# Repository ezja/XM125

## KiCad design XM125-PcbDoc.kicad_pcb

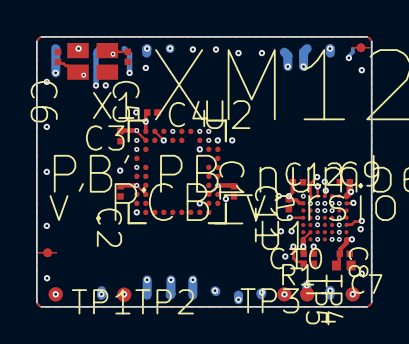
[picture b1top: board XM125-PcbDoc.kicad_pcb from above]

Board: 4 copper layers, 18.6 x 15.0 mm, 24 parts (1 on the bottom side), 28 nets.

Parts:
C1, C2, C3, C4, C12: Generic 1uF SMD capacitor, metric 0603 (0201); CAPC0603X04L_no_silkscreen
C5, C6: Generic 8pF SMD capacitor, metric 0603 (0201); CAPC0603X04L_no_silkscreen
C7: Generic 4.7uF SMD capacitor, metric 1005 (0402); CAPC1005X05L
C8, C9, C10, C11: Generic 100 nF SMD capacitor, metric 0603 (0201); CAPC0603X04L_no_silkscreen
F1, F2: Fiducial marker; Fiducial 0.5 mm footprint-1
J1: 28-pin Land Grid Array (LGA), pitch 1.27 mm; LCCS127P1500X1800X0-28N
R1: 100 kOhm generic SMD resistor, +/-1%, metric 0603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; RESC0603X03L_no_silkscreen
TP1, TP2, TP3, TP4, TP5: Circular test point; Testpoint_circular_0.8_no_silkscreen
U1: RISC Microcontroller, 32-Bit, FLASH, 80MHz, CMOS,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; BGA49C40P7X7_314X313X58
U2: Acconeer A121 pulsed coherent 60 GHz radar sensor; BGA50C50P10X10_520X550X90
X1: Crystal 24 MHz 2.5 x 2.0 mm 4-SMD; ECS-240-8-36-RWN-TR3-Footprint-No-Silk

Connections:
1V8_sensor: C1.1, C2.1, C3.1, J1.3, U2.C2, U2.C9, U2.D1, U2.D10, U2.J9
DEBUG_UART_RX: J1.21, U1.C2
DEBUG_UART_TX: J1.23, U1.D2
ENABLE: U1.F1, U2.F10
GND: C1.2, C2.2, C3.2, C4.2, C5.2, C6.2, C7.2, C8.2, C9.2, C10.2, C11.2, C12.2, J1.2, J1.4, J1.7, J1.10, J1.13, J1.16, J1.19, J1.22, J1.27, R1.1, TP2.1, U1.A6, U1.B1, U1.E7, U1.G2, U2.A2, U2.A3, U2.A4, U2.A5, U2.A6, U2.A7, U2.A8, U2.A9, U2.B1, U2.B2, U2.B9, U2.B10, U2.C1, U2.C10, U2.D2, U2.D9, U2.E1, U2.E2, U2.E9, U2.E10, U2.F1, U2.F2, U2.F9, U2.G1, U2.G10, U2.H1, U2.H2, U2.H9, U2.J3, U2.J5, U2.J6, U2.J8, U2.K4, U2.K5, U2.K7, X1.2, X1.4
I2C_ADDR: J1.20, U1.D7
I2C_SCL: J1.17, U1.E3
I2C_SDA: J1.18, U1.F2
INTERRUPT: U1.A3, U2.K8
MCU_INT: J1.28, U1.C5
MISC_GPIO0: J1.24, U1.G4
MISC_GPIO1: J1.25, U1.G6
MISC_GPIO2_BOOT0: J1.26, R1.2, U1.A5
NRESET: J1.14, TP5.1, U1.D5
SPI_CLK: U1.F5, U2.K2
SPI_MISO: U1.F4, U2.K3
SPI_MOSI: U1.F3, U2.K6
SPI_SS: U1.G5, U2.J2
SWDCLK: J1.12, TP4.1, U1.A2
SWDIO: J1.11, TP3.1, U1.B2
UART_CTS: J1.8, U1.F6
UART_RTS: J1.9, U1.G7
UART_RX: J1.6, U1.E4
UART_TX: J1.5, U1.E5
VIN_sensor: C4.1, C7.1, C8.1, C9.1, C10.1, C11.1, C12.1, J1.1, TP1.1, U1.A1, U1.A7, U1.B6, U1.F7, U1.G1, U2.J1, U2.K9
WAKE_UP: J1.15, U1.C1
XIN: C5.1, U2.J10, X1.3
XOUT: C6.1, U2.H10, X1.1
